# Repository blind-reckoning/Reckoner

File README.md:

<p align="center">
  <picture>
    <source media="(prefers-color-scheme: dark)" srcset="brand/logos/lockup-reversed.svg">
    
  </picture>
</p>

<p align="center">
  <strong>Turns press-and-hold motorised blinds into Home Assistant covers.</strong><br>
  One Reckoner per blind, hidden in the wall box behind the buttons you already have.
</p>

<p align="center">

</p>

> [!CAUTION]
> **This board switches 230 VAC mains and is not isolated.** Every part of it, including the ESP32 and the programming pads, is live whenever it is connected. A mistake can **kill you** or **start a fire inside your wall**. If you are not qualified to work on mains wiring, do not build or install it. Read [Safety](#safety) first.

## What it does

Motorised blinds with press-and-hold buttons have no idea where they are. The Reckoner sits in the wall box between those buttons and the motor, and fixes that.

- **Your buttons keep working, with or without Wi-Fi.** One press runs the blind to the end; another press stops it.
- **For Home Assistant.** The blind is a cover: open, close, stop, set position and report position.
- **It knows where the blind is, without a sensor.** It uses **dead reckoning**: a known start, the calibrated time for a full stroke and the time elapsed. At each end the motor's limit switch cuts the current; the Reckoner sees the drop, takes a **fix** and clears the **drift**.
- **It survives power cuts.** It notices mains loss within one cycle and saves the position on the energy left in its capacitors.

## How it works

| Block | Main parts |
|---|---|
| Mains input | 2 A slow-blow fuse, 275 VAC varistor; circuit ground is mains L |
| Supply | LNK3206D off-line buck to 5 V (no transformer), AP2112K-3.3 |
| Microcontroller | ESP32-C6-MINI-1: Wi-Fi 6, Bluetooth LE, Thread |
| Metering | HLW8110 and a 10 mΩ shunt: motor current and mains voltage |
| Motor relays | K1 HF46F-G switches the motor, K2 G5Q-14 picks the direction |
| Inputs | Resistor dividers and BAT54S clamps for the buttons and every mains cycle |

K2's common is fed through K1, so **up and down can never be live at the same time**, not even with a firmware bug or a welded contact. Both relays are held off by hardware through reset, boot and flashing.

The board is 70 × 54.5 mm on two layers, routed by hand, with 3 to 5 mm between mains nodes. The production files for JLCPCB are in [`PCB/production/`](PCB/production/).

## Bill of materials

| Item | Qty | Supplier | Price (USD) |
|---|---|---|---|
| Per-part BOM [`BOM/bom.csv`](BOM/bom.csv), order lists for [LCSC](BOM/bom-lcsc.csv) and [Digi-Key](BOM/bom-digikey.csv), quote screenshots in [`BOM/`](BOM/) | 1 | — | 0.00 |
| PCB: 2 layers, 70 × 54.5 mm, 1.6 mm, green, lead-free HASL (5 boards) | 1 | JLCPCB | 6.25 |
| SMT stencil, top side, with frame | 1 | JLCPCB | 16.75 |
| Parts for one board, with LCSC minimum order quantities | 1 | LCSC | 29.24 |
| Parts for one board: U3 and R11/R12/R15 | 1 | Digi-Key | 4.77 |
| Shipping and taxes | | All | 89.74 |
| **Total** | | | **146.75** |

Shipping and taxes: JLCPCB $24.28 (after a $10 coupon), LCSC $30.17 (shipping and tariff, after $3.05 of discounts), Digi-Key $35.29 (€25.00 shipping and €6.44 VAT). The same table is in [`bom.csv`](bom.csv).

## Safety

> [!WARNING]
> **There is no low-voltage side.** Circuit ground is mains live (L), so the ESP32, the LED, the test pads and every trace sit at 230 VAC to earth whenever L and N are connected. Only the enclosure protects you.

- **"Off" is not safe.** Only isolating the circuit at the breaker makes the board dead, and C1 and C2 (400 V) can stay charged after that: measure them before you touch it. The motor wires J5 and J6 reach about 460 VAC while the motor runs.
- **Never connect USB, a debugger, a laptop or a grounded probe while it is on mains.** Their ground is earth; this board's ground is L.
- **Never touch it while it is connected**, not even "just the logic side". There is no logic side. There is only the death side!
- **Never power it without an insulating enclosure**, and never mount it in a metal box.
- **Never work on live mains alone.** Have someone with you who can give first aid.
- **Installing:** leave it to a qualified electrician, and isolate and prove dead first. The circuit needs a breaker of 16 A or less and a 30 mA RCD.
  - J1 goes to L and J2 to N (they can't be swapped). The buttons' common must be on the same L as J1.
  - J3 and J4 go to the button outputs, J5 and J6 to the motor's up and down wires. The motor's neutral stays on house N.
  - The motor must be a 230 VAC tubular motor of about 1 A with its own limit switches.
- **Flashing and testing:** flash only with mains disconnected at the source, through the USB pads TP1 to TP4 (TP5 to GND for download mode); after that, updates go over the air. Test live only through an isolation transformer and a series-lamp limiter, with isolated probes.

> [!IMPORTANT]
> Blind Reckoning is a hobby prototype I built for Hack Club Half Life. It is **not a certified product** and has **not been tested by any laboratory**. Everything here is provided as is, without warranty. **If you build, flash, test or install a Reckoner, you do so entirely at your own risk.** The authors accept no responsibility for injury, death, fire or damage to property.
>
> The **Blind Reckoning** "brand" is just a game. Please do not take it too seriously ;)

## Status

Designed, routed and costed; boards and parts are next to order. The enclosure (`CAD/`) and firmware (`Firmware/`) are not started.

## Licence

| What | Licence |
|---|---|
| Hardware: `PCB/`, `CAD/` and `BOM/bom.csv` | [CERN-OHL-S-2.0](LICENSE) |
| Documentation: this README and `docs/` | [CC BY-SA 4.0](LICENSE-DOCS) |
| Firmware | not written yet |

These licences apply retroactively: any copy of the hardware or documentation from any commit of this repository, including commits made before the licence files were added on 2 October 2026, is licensed under these terms.

Copyright 2026 KOZELJ Michele. Source location: <https://github.com/blind-reckoning/Reckoner>. If you make hardware from this source, keep the source location visible on the board or enclosure where practicable (CERN-OHL-S v2, section 4).

Not covered: the Blind Reckoning name and logos (`brand/logos/`, `brand/symbols/`), which are not licensed for reuse, so modified hardware needs its own name (see the [brand book](brand/README.md)); the fonts in `brand/fonts/` (SIL Open Font License 1.1); and KiCad's library symbols and footprints (KiCad library licence).

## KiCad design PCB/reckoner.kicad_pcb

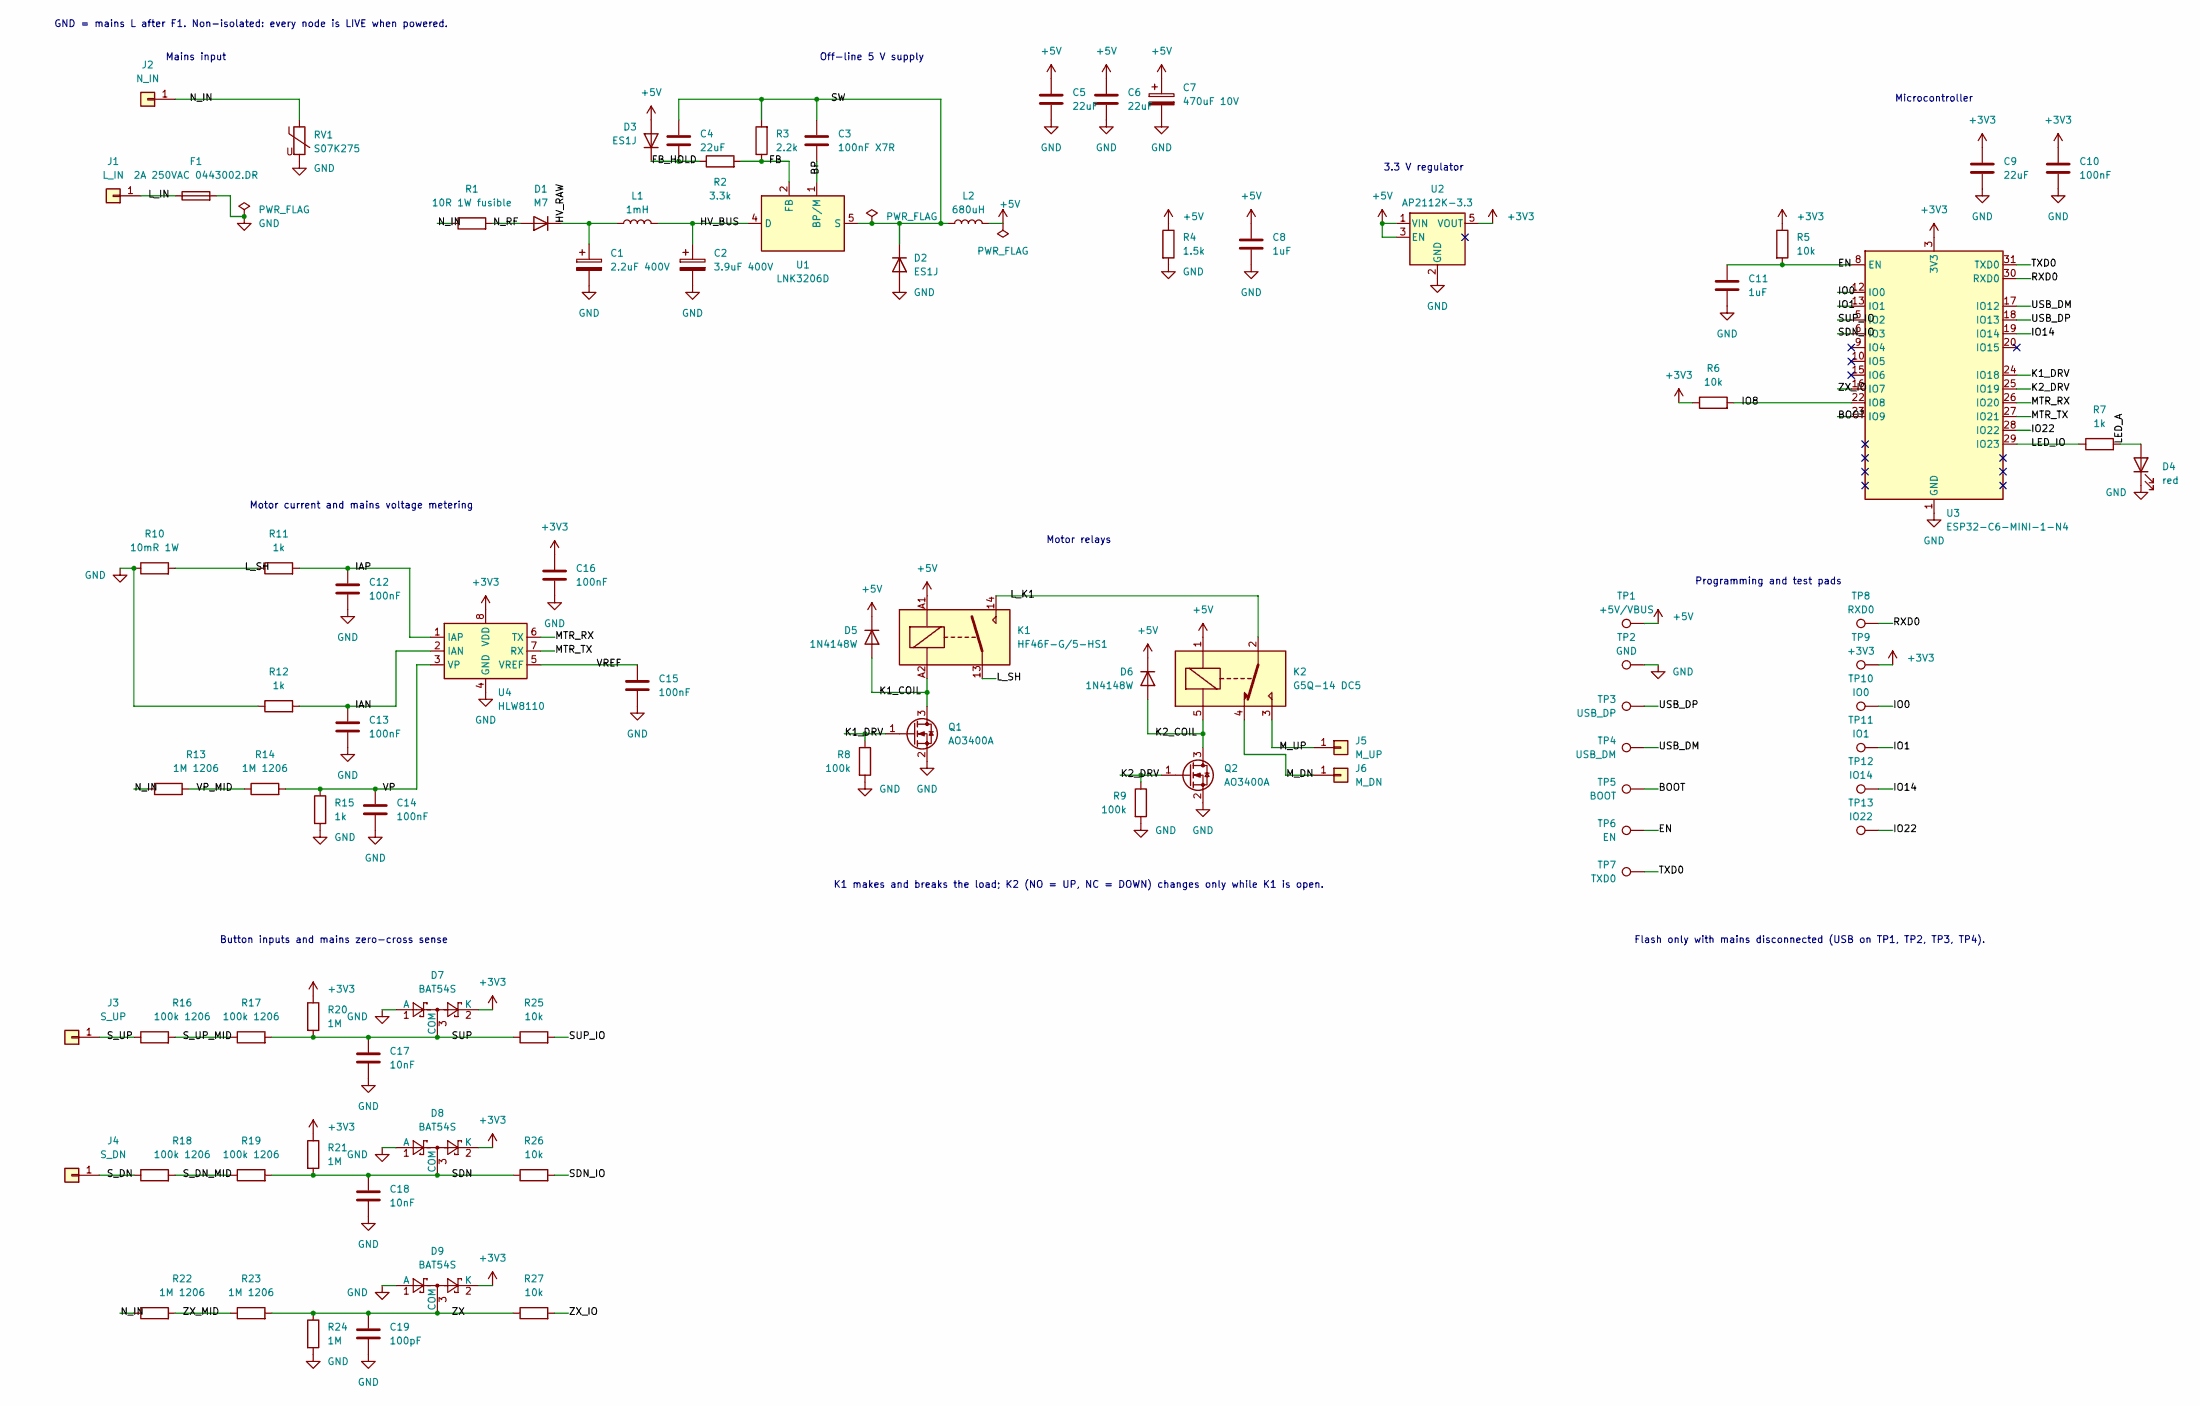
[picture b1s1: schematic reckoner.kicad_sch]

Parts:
C1: 2.2uF 400V; CP_Elec_6.3x9.9; LCSC C48970947
C2: 3.9uF 400V; CP_Elec_8x10; LCSC C33129636
C3: 100nF X7R; C_0603_1608Metric; LCSC C14663
C4, C9: 22uF; C_0805_2012Metric; LCSC C45783
C5, C6: 22uF; C_1206_3216Metric; LCSC C12891
C7: 470uF 10V; CP_Elec_8x10; LCSC C2693598
C8, C11: 1uF; C_0402_1005Metric; LCSC C52923
C10, C12, C13, C14, C15, C16: 100nF; C_0402_1005Metric; LCSC C1525
C17, C18: 10nF; C_0402_1005Metric; LCSC C15195
C19: 100pF; C_0402_1005Metric; LCSC C1546
D1: M7; D_SMA; LCSC C95872
D2, D3: ES1J; D_SMA; LCSC C86560
D4: red; LED_0603_1608Metric; LCSC C2286
D5, D6: 1N4148W; D_SOD-123; LCSC C81598
D7, D8, D9: BAT54S; SOT-23; LCSC C8592
F1: 2A 250VAC 0443002.DR; FUSE-SMD_L10.1-W3.1; LCSC C187538
J1: L_IN; SolderWire-0.75sqmm_1x01_D1.25mm_OD2.3mm
J2: N_IN; SolderWire-0.75sqmm_1x01_D1.25mm_OD2.3mm
J3: S_UP; SolderWire-0.75sqmm_1x01_D1.25mm_OD2.3mm
J4: S_DN; SolderWire-0.75sqmm_1x01_D1.25mm_OD2.3mm
J5: M_UP; SolderWire-0.75sqmm_1x01_D1.25mm_OD2.3mm
J6: M_DN; SolderWire-0.75sqmm_1x01_D1.25mm_OD2.3mm
K1: HF46F-G/5-HS1; Relay_SPST_Omron_G5NB; LCSC C165255
K2: G5Q-14 DC5; Relay_SPDT_Omron-G5Q-1; LCSC C397241
L1: 1mH; L_Taiyo-Yuden_NR-50xx; LCSC C5339706
L2: 680uH; IND-TH_BD9.5-P5.20-D0.6; LCSC C2924238
Q1, Q2: AO3400A; SOT-23; LCSC C20917
R1: 10R 1W fusible; R_Axial_DIN0309_L9.0mm_D3.2mm_P2.54mm_Vertical; LCSC C145951
R2: 3.3k; R_0402_1005Metric; LCSC C25890
R3: 2.2k; R_0402_1005Metric; LCSC C25879
R4: 1.5k; R_0603_1608Metric; LCSC C22843
R5, R6, R25, R26, R27: 10k; R_0402_1005Metric; LCSC C25744
R7: 1k; R_0603_1608Metric; LCSC C21190
R8, R9: 100k; R_0402_1005Metric; LCSC C25741
R10: 10mR 1W; R_1206_3216Metric; LCSC C105362
R11, R12, R15: 1k; R_0402_1005Metric; LCSC C11702
R13, R14, R22, R23: 1M 1206; R_1206_3216Metric; LCSC C17927
R16, R17, R18, R19: 100k 1206; R_1206_3216Metric; LCSC C17900
R20, R21, R24: 1M; R_0402_1005Metric; LCSC C26083
RV1: S07K275; RES-TH_L9.0-W4.6-P5.00-D0.6-S1.60; LCSC C1527389
TP1: +5V/VBUS; TestPoint_Pad_D1.0mm
TP2: GND; TestPoint_Pad_D1.0mm
TP3: USB_DP; TestPoint_Pad_D1.0mm
TP4: USB_DM; TestPoint_Pad_D1.0mm
TP5: BOOT; TestPoint_Pad_D1.0mm
TP6: EN; TestPoint_Pad_D1.0mm
TP7: TXD0; TestPoint_Pad_D1.0mm
TP8: RXD0; TestPoint_Pad_D1.0mm
TP9: +3V3; TestPoint_Pad_D1.0mm
TP10: IO0; TestPoint_Pad_D1.0mm
TP11: IO1; TestPoint_Pad_D1.0mm
TP12: IO14; TestPoint_Pad_D1.0mm
TP13: IO22; TestPoint_Pad_D1.0mm
U1: LNK3206D; PowerIntegrations_SO-8C; LCSC C2987730
U2: AP2112K-3.3; SOT-23-5; LCSC C51118
U3: ESP32-C6-MINI-1-N4; ESP32-C6-MINI-1; LCSC C5736265
U4: HLW8110; SOIC-8_3.9x4.9mm_P1.27mm; LCSC C970139

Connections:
+3V3: C9.1, C10.1, C16.1, D7.2 (K), D8.2 (K), D9.2 (K), R5.1, R6.1, R20.1, R21.1, TP9.1 (1_1), U2.5 (VOUT), U3.3 (3V3), U4.8 (VDD)
+5V: C5.1, C6.1, C7.1, C8.1, D3.2 (A), D5.1 (K), D6.1 (K), K1.A1, K2.1, L2.2, R4.1, TP1.1 (1_1), U2.1 (VIN), U2.3 (EN)
/BOOT: TP5.1 (1_1), U3.23 (IO9)
/BP: C3.1, U1.1 (BP/M)
/EN: C11.1, R5.2, TP6.1 (1_1), U3.8 (EN)
/FB: R2.2, R3.1, U1.2 (FB)
/FB_HOLD: C4.1, D3.1 (K), R2.1
/HV_BUS: C2.1, L1.2, U1.4 (D)
/HV_RAW: C1.1, D1.1 (K), L1.1
/IAN: C13.1, R12.2, U4.2 (IAN)
/IAP: C12.1, R11.2, U4.1 (IAP)
/IO0: TP10.1 (1_1), U3.12 (IO0)
/IO1: TP11.1 (1_1), U3.13 (IO1)
/IO8: R6.2, U3.22 (IO8)
/IO14: TP12.1 (1_1), U3.19 (IO14)
/IO22: TP13.1 (1_1), U3.28 (IO22)
/K1_COIL: D5.2 (A), K1.A2, Q1.3 (D)
/K1_DRV: Q1.1 (G), R8.1, U3.24 (IO18)
/K2_COIL: D6.2 (A), K2.5, Q2.3 (D)
/K2_DRV: Q2.1 (G), R9.1, U3.25 (IO19)
/LED_A: D4.2 (A), R7.2
/LED_IO: R7.1, U3.29 (IO23)
/L_IN: F1.1, J1.1 (Pin_1_1)
/L_K1: K1.14, K2.2
/L_SH: K1.13, R10.2, R11.1
/MTR_RX: U3.26 (IO20), U4.6 (TX)
/MTR_TX: U3.27 (IO21), U4.7 (RX)
/M_DN: J6.1 (Pin_1_1), K2.4
/M_UP: J5.1 (Pin_1_1), K2.3
/N_IN: J2.1 (Pin_1_1), R1.1, R13.1, R22.1, RV1.1
/N_RF: D1.2 (A), R1.2
/RXD0: TP8.1 (1_1), U3.30 (RXD0)
/SDN: C18.1, D8.3 (COM), R19.2, R21.2, R26.1
/SDN_IO: R26.2, U3.6 (IO3)
/SUP: C17.1, D7.3 (COM), R17.2, R20.2, R25.1
/SUP_IO: R25.2, U3.5 (IO2)
/SW: C3.2, C4.2, D2.1 (K), L2.1, R3.2, U1.5 (S), U1.6 (S), U1.7 (S), U1.8 (S)
/S_DN: J4.1 (Pin_1_1), R18.1
/S_DN_MID: R18.2, R19.1
/S_UP: J3.1 (Pin_1_1), R16.1
/S_UP_MID: R16.2, R17.1
/TXD0: TP7.1 (1_1), U3.31 (TXD0)
/USB_DM: TP4.1 (1_1), U3.17 (IO12)
/USB_DP: TP3.1 (1_1), U3.18 (IO13)
/VP: C14.1, R14.2, R15.1, U4.3 (VP)
/VP_MID: R13.2, R14.1
/VREF: C15.1, U4.5 (VREF)
/ZX: C19.1, D9.3 (COM), R23.2, R24.1, R27.1
/ZX_IO: R27.2, U3.16 (IO7)
/ZX_MID: R22.2, R23.1
GND: C1.2, C2.2, C5.2, C6.2, C7.2, C8.2, C9.2, C10.2, C11.2, C12.2, C13.2, C14.2, C15.2, C16.2, C17.2, C18.2, C19.2, D2.2 (A), D4.1 (K), D7.1 (A), D8.1 (A), D9.1 (A), F1.2, Q1.2 (S), Q2.2 (S), R4.2, R8.2, R9.2, R10.1, R12.1, R15.2, R24.2, RV1.2, TP2.1 (1_1), U2.2 (GND), U3.1 (GND), U3.2 (GND), U3.11 (GND), U3.14 (GND), U3.36 (GND), U3.37 (GND), U3.38 (GND), U3.39 (GND), U3.40 (GND), U3.41 (GND), U3.42 (GND), U3.43 (GND), U3.44 (GND), U3.45 (GND), U3.46 (GND), U3.47 (GND), U3.48 (GND), U3.49 (GND), U3.50 (GND), U3.51 (GND), U3.52 (GND), U3.53 (GND), U4.4 (GND)

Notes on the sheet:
Microcontroller
Motor current and mains voltage metering
K1 makes and breaks the load; K2 (NO = UP, NC = DOWN) changes only while K1 is open.
Button inputs and mains zero-cross sense
3.3 V regulator
Mains input
Programming and test pads
Off-line 5 V supply
GND = mains L after F1. Non-isolated: every node is LIVE when powered.
Motor relays
Flash only with mains disconnected (USB on TP1, TP2, TP3, TP4).

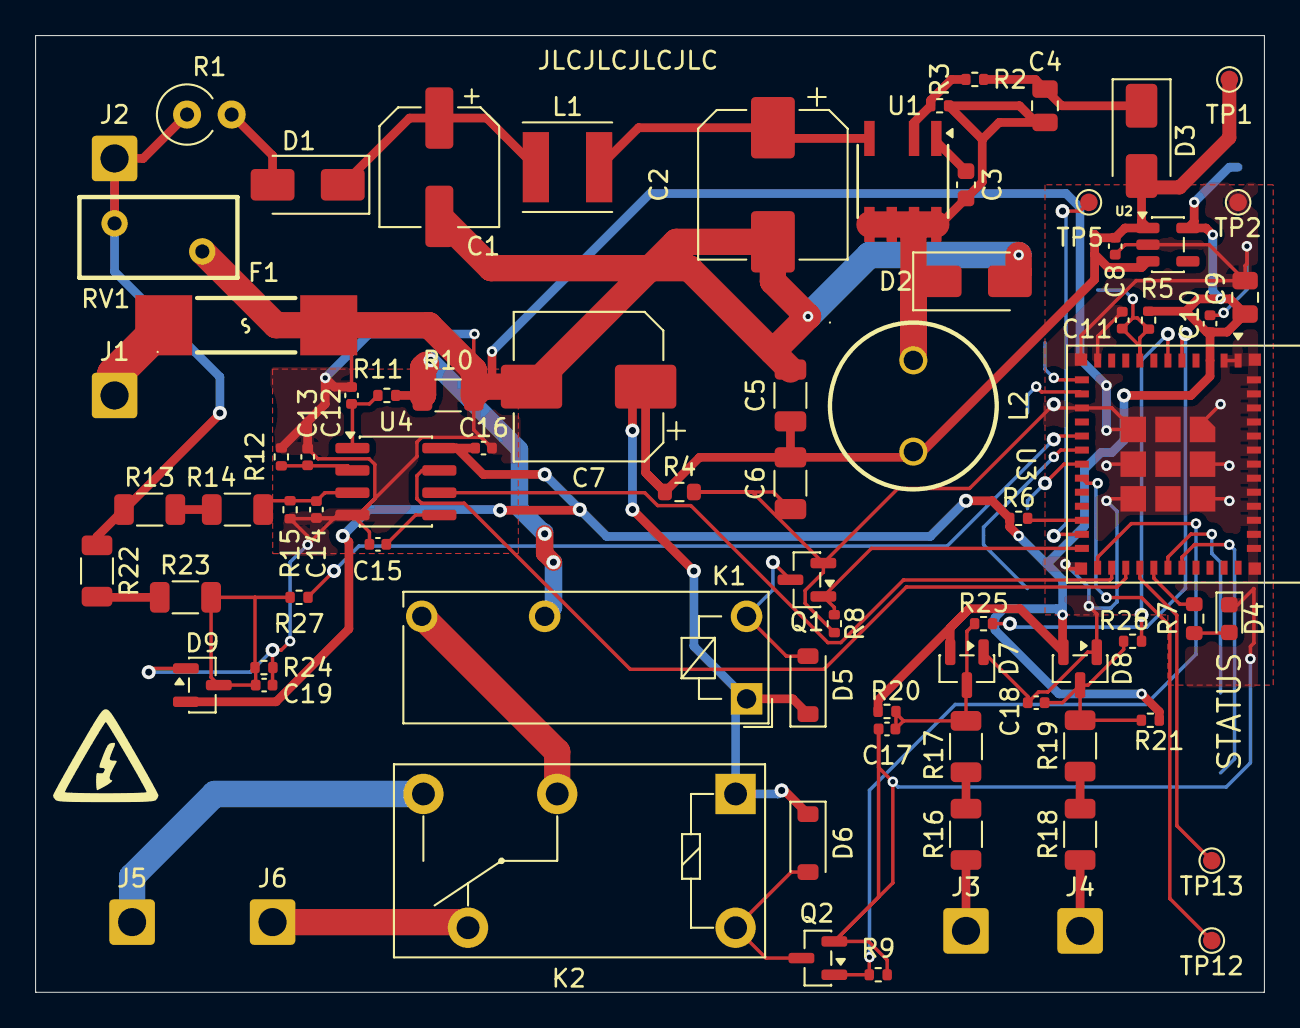
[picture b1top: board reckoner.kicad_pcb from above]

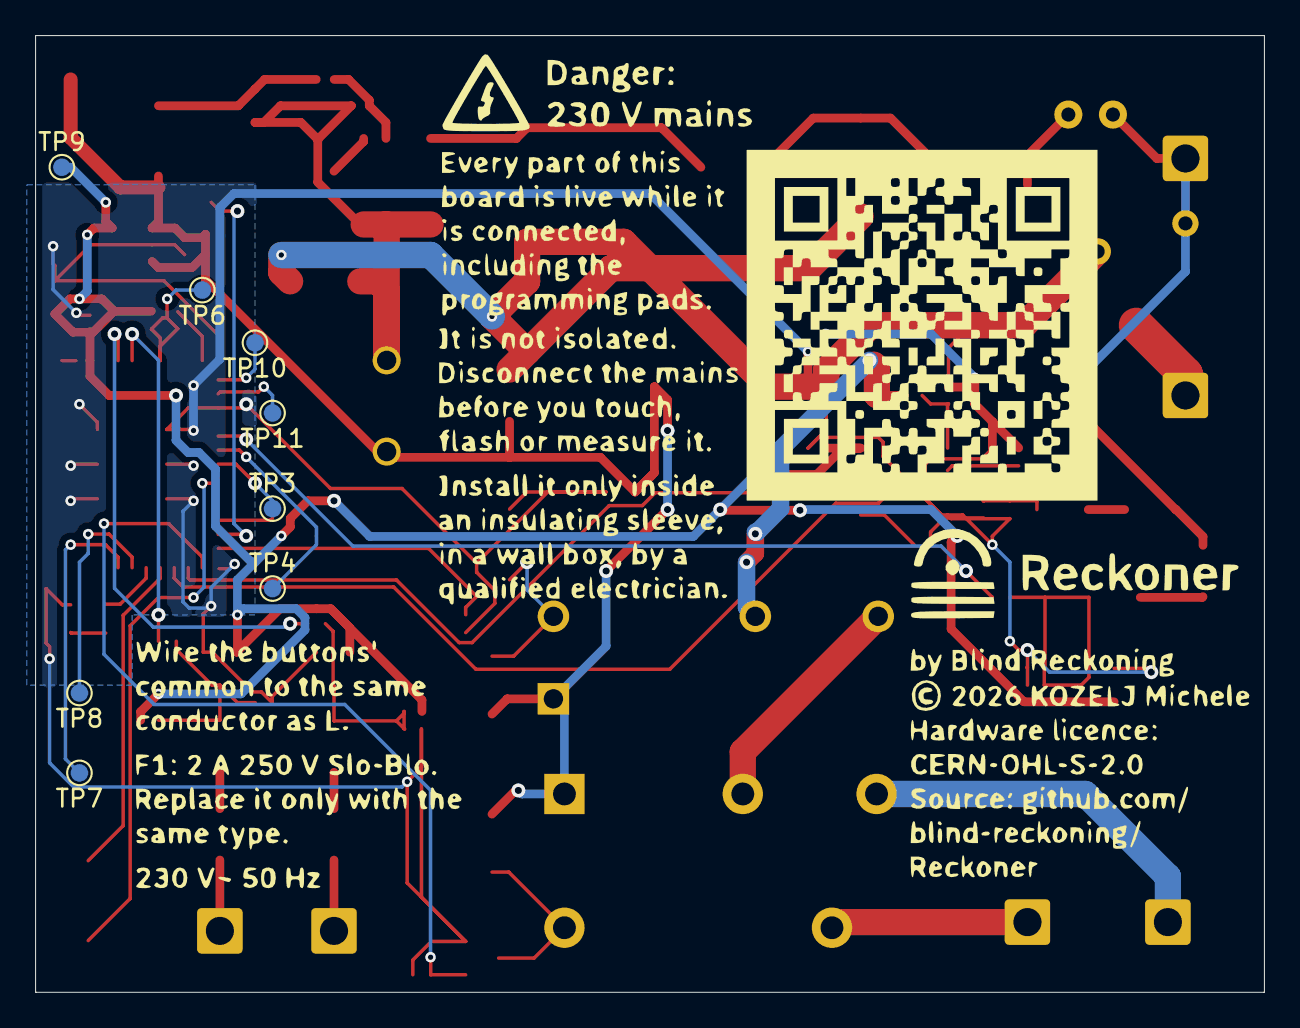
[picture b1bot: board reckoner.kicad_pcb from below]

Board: 2 copper layers, 70.0 x 54.5 mm, 86 parts (8 on the bottom side), 51 nets.

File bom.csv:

Comment,Designator,Footprint,LCSC Part #,Quantity,Unit Price (USD),Total (USD),JLCPCB Library,Assembly,Rating,Purpose,Link
"Littelfuse 0443002.DR, 2 A Slo-Blo",F1,FUSE-SMD_L10.1-W3.1,C187538,1,0.7999,0.7999,Extended,SMT,"250 VAC, 50 A breaking",Mains entry,https://www.lcsc.com/product-detail/C187538.html
TDK B72207S2271K101 (S07K275),RV1,RES-TH_L9.0-W4.6-P5.00-D0.6-S1.60,C1527389,1,0.0808,0.0808,Extended,THT,"275 VAC, 430 V, 1.75 kA",Mains entry,https://www.lcsc.com/product-detail/C1527389.html
FR1WS 10 Ω fusible,R1,R_Axial_DIN0309_L9.0mm_D3.2mm_P2.54mm_Vertical,C145951,1,0.0374,0.0374,Extended,THT,"1 W, 250 V",Power supply,https://www.lcsc.com/product-detail/C145951.html
M7,D1,D_SMA,C95872,1,0.0102,0.0102,Basic,SMT,"1000 V, 1 A, IFSM 30 A",Power supply,https://www.lcsc.com/product-detail/C95872.html
"2.2 µF, RYUD400V2.2UF6*10",C1,CP_Elec_6.3x9.9,C48970947,1,0.0800,0.0800,Extended,SMT,"400 V, 105 °C, 6000 h, 13 mA at 120 Hz",Power supply,https://www.lcsc.com/product-detail/C48970947.html
"3.9 µF, FOLLON EFVD400ADA3R9M08B0",C2,CP_Elec_8x10,C33129636,1,0.1376,0.1376,Extended,SMT,"400 V, 105 °C, 5000 h, 64 mA at 120 Hz",Power supply,https://www.lcsc.com/product-detail/C33129636.html
"1 mH, XRNR5040-1mH/M",L1,L_Taiyo-Yuden_NR-50xx,C5339706,1,0.0648,0.0648,Extended,SMT,"250 mA, 6.2 Ω",Power supply,https://www.lcsc.com/product-detail/C5339706.html
LNK3206D-TL,U1,PowerIntegrations_SO-8C,C2987730,1,1.0762,1.0762,Extended,SMT,"725 V drain, ILIMIT 450–650 mA (standard)",Power supply,https://www.lcsc.com/product-detail/C2987730.html
100 nF X7R,C3,C_0603_1608Metric,C14663,1,0.0123,0.0123,Basic,SMT,50 V,Power supply,https://www.lcsc.com/product-detail/C14663.html
ES1J-LTP,"D2,D3",D_SMA,C86560,2,0.0218,0.0436,Extended,SMT,"600 V, 1 A, trr 35 ns",Power supply,https://www.lcsc.com/product-detail/C86560.html
"680 µH, PDPTAT0810-681K",L2,IND-TH_BD9.5-P5.20-D0.6,C2924238,1,0.1179,0.1179,Extended,THT,"Irms 350 mA, Isat 800 mA, 0.91 Ω",Power supply,https://www.lcsc.com/product-detail/C2924238.html
22 µF X5R,"C4,C9",C_0805_2012Metric,C45783,2,0.2202,0.4404,Basic,SMT,25 V,Power supply; MCU,https://www.lcsc.com/product-detail/C45783.html
3.3 kΩ 1 %,R2,R_0402_1005Metric,C25890,1,0.0035,0.0035,Basic,SMT,62.5 mW,Power supply,https://www.lcsc.com/product-detail/C25890.html
2.2 kΩ 1 %,R3,R_0402_1005Metric,C25879,1,0.0013,0.0013,Basic,SMT,62.5 mW,Power supply,https://www.lcsc.com/product-detail/C25879.html
22 µF X5R,"C5,C6",C_1206_3216Metric,C12891,2,0.1733,0.3466,Basic,SMT,25 V,Power supply,https://www.lcsc.com/product-detail/C12891.html
"470 µF, BXJ10V470UF8*10",C7,CP_Elec_8x10,C2693598,1,0.2346,0.2346,Extended,SMT,"10 V, 105 °C, 5000 h, 160 mΩ",Power supply,https://www.lcsc.com/product-detail/C2693598.html
1.5 kΩ 1 %,R4,R_0603_1608Metric,C22843,1,0.0020,0.0020,Basic,SMT,100 mW,Power supply,https://www.lcsc.com/product-detail/C22843.html
AP2112K-3.3TRG1,U2,SOT-23-5,C51118,1,0.1710,0.1710,Extended,SMT,"600 mA, 6 V max in",3.3 V LDO,https://www.lcsc.com/product-detail/C51118.html
1 µF X5R,"C8,C11",C_0402_1005Metric,C52923,2,0.0099,0.0198,Basic,SMT,25 V,3.3 V LDO; MCU,https://www.lcsc.com/product-detail/C52923.html
100 nF X7R,"C10,C12,C13,C14,C15,C16",C_0402_1005Metric,C1525,6,0.0045,0.0270,Basic,SMT,16 V,MCU; Metering,https://www.lcsc.com/product-detail/C1525.html
ESP32-C6-MINI-1-N4,U3,ESP32-C6-MINI-1,C5736265,1,3.8854,3.8854,Extended,SMT,"3.0–3.6 V, 354 mA TX peak",MCU,https://www.lcsc.com/product-detail/C5736265.html
10 kΩ 1 %,"R5,R6,R25,R26,R27",R_0402_1005Metric,C25744,5,0.0034,0.0170,Basic,SMT,62.5 mW,MCU; Inputs,https://www.lcsc.com/product-detail/C25744.html
KT-0603R red,D4,LED_0603_1608Metric,C2286,1,0.0076,0.0076,Basic,SMT,20 mA max,MCU,https://www.lcsc.com/product-detail/C2286.html
1 kΩ 1 %,R7,R_0603_1608Metric,C21190,1,0.0026,0.0026,Basic,SMT,100 mW,MCU,https://www.lcsc.com/product-detail/C21190.html
Hongfa HF46F-G/5-HS1,K1,Relay_SPST_Omron_G5NB,C165255,1,1.1852,1.1852,Extended,THT,"5 V coil 200 mW (125 Ω), 10 A 250 VAC",Motor switching,https://www.lcsc.com/product-detail/C165255.html
Omron G5Q-14 DC5,K2,Relay_SPDT_Omron-G5Q-1,C397241,1,1.1396,1.1396,Extended,THT,"5 V coil 400 mW, SPDT 3 A 250 VAC (NO and NC); 1000 VAC across open contacts",Motor switching,https://www.lcsc.com/product-detail/C397241.html
AO3400A,"Q1,Q2",SOT-23,C20917,2,0.0888,0.1776,Basic,SMT,"30 V, 5.7 A, 48 mΩ @ 2.5 V",Motor switching,https://www.lcsc.com/product-detail/C20917.html
100 kΩ 1 %,"R8,R9",R_0402_1005Metric,C25741,2,0.0024,0.0048,Basic,SMT,62.5 mW,Motor switching,https://www.lcsc.com/product-detail/C25741.html
1N4148W,"D5,D6",D_SOD-123,C81598,2,0.0123,0.0246,Basic,SMT,"75 V, 150 mA",Motor switching,https://www.lcsc.com/product-detail/C81598.html
"10 mΩ 1 %, FMF06FTHR010-LH",R10,R_1206_3216Metric,C105362,1,0.0410,0.0410,Extended,SMT,1 W,Metering,https://www.lcsc.com/product-detail/C105362.html
HLW8110,U4,SOIC-8_3.9x4.9mm_P1.27mm,C970139,1,0.6877,0.6877,Extended,SMT,"3.0–3.6 V, ±800 mV/PGA inputs",Metering,https://www.lcsc.com/product-detail/C970139.html
1 kΩ 1 %,"R11,R12,R15",R_0402_1005Metric,C11702,3,0.0018,0.0054,Basic,SMT,62.5 mW,Metering,https://www.lcsc.com/product-detail/C11702.html
1 MΩ 1 %,"R13,R14,R22,R23",R_1206_3216Metric,C17927,4,0.0041,0.0164,Basic,SMT,"250 mW, 200 V",Metering; Inputs,https://www.lcsc.com/product-detail/C17927.html
100 kΩ 1 %,"R16,R17,R18,R19",R_1206_3216Metric,C17900,4,0.0102,0.0408,Basic,SMT,"250 mW, 200 V",Inputs,https://www.lcsc.com/product-detail/C17900.html
1 MΩ 1 %,"R20,R21,R24",R_0402_1005Metric,C26083,3,0.0026,0.0078,Basic,SMT,62.5 mW,Inputs,https://www.lcsc.com/product-detail/C26083.html
10 nF X7R,"C17,C18",C_0402_1005Metric,C15195,2,0.0050,0.0100,Basic,SMT,50 V,Inputs,https://www.lcsc.com/product-detail/C15195.html
BAT54S,"D7,D8,D9",SOT-23,C8592,3,0.0231,0.0693,Extended,SMT,"30 V, 200 mA",Inputs,https://www.lcsc.com/product-detail/C8592.html
100 pF C0G,C19,C_0402_1005Metric,C1546,1,0.0042,0.0042,Basic,SMT,50 V,Inputs,https://www.lcsc.com/product-detail/C1546.html

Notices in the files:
README.md:
Hardware licence: CERN-OHL-S-2.0
